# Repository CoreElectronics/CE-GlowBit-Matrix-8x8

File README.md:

# GlowBit™ Matrix 8x8

This is the repo for the Core Electronics [GlowBit Matrix 8x8](https://core-electronics.com.au/catalog/product/view/sku/ce08033).

## License
This project is open source - please review the LICENSE.md file for further licensing information.

If you have any technical questions, or concerns about licensing, please contact technical support on the [Core Electronics forums](https://forum.core-electronics.com.au/).

*\"GlowBit\" and the GlowBit logo are trademarks of Core Electronics Pty Ltd.*

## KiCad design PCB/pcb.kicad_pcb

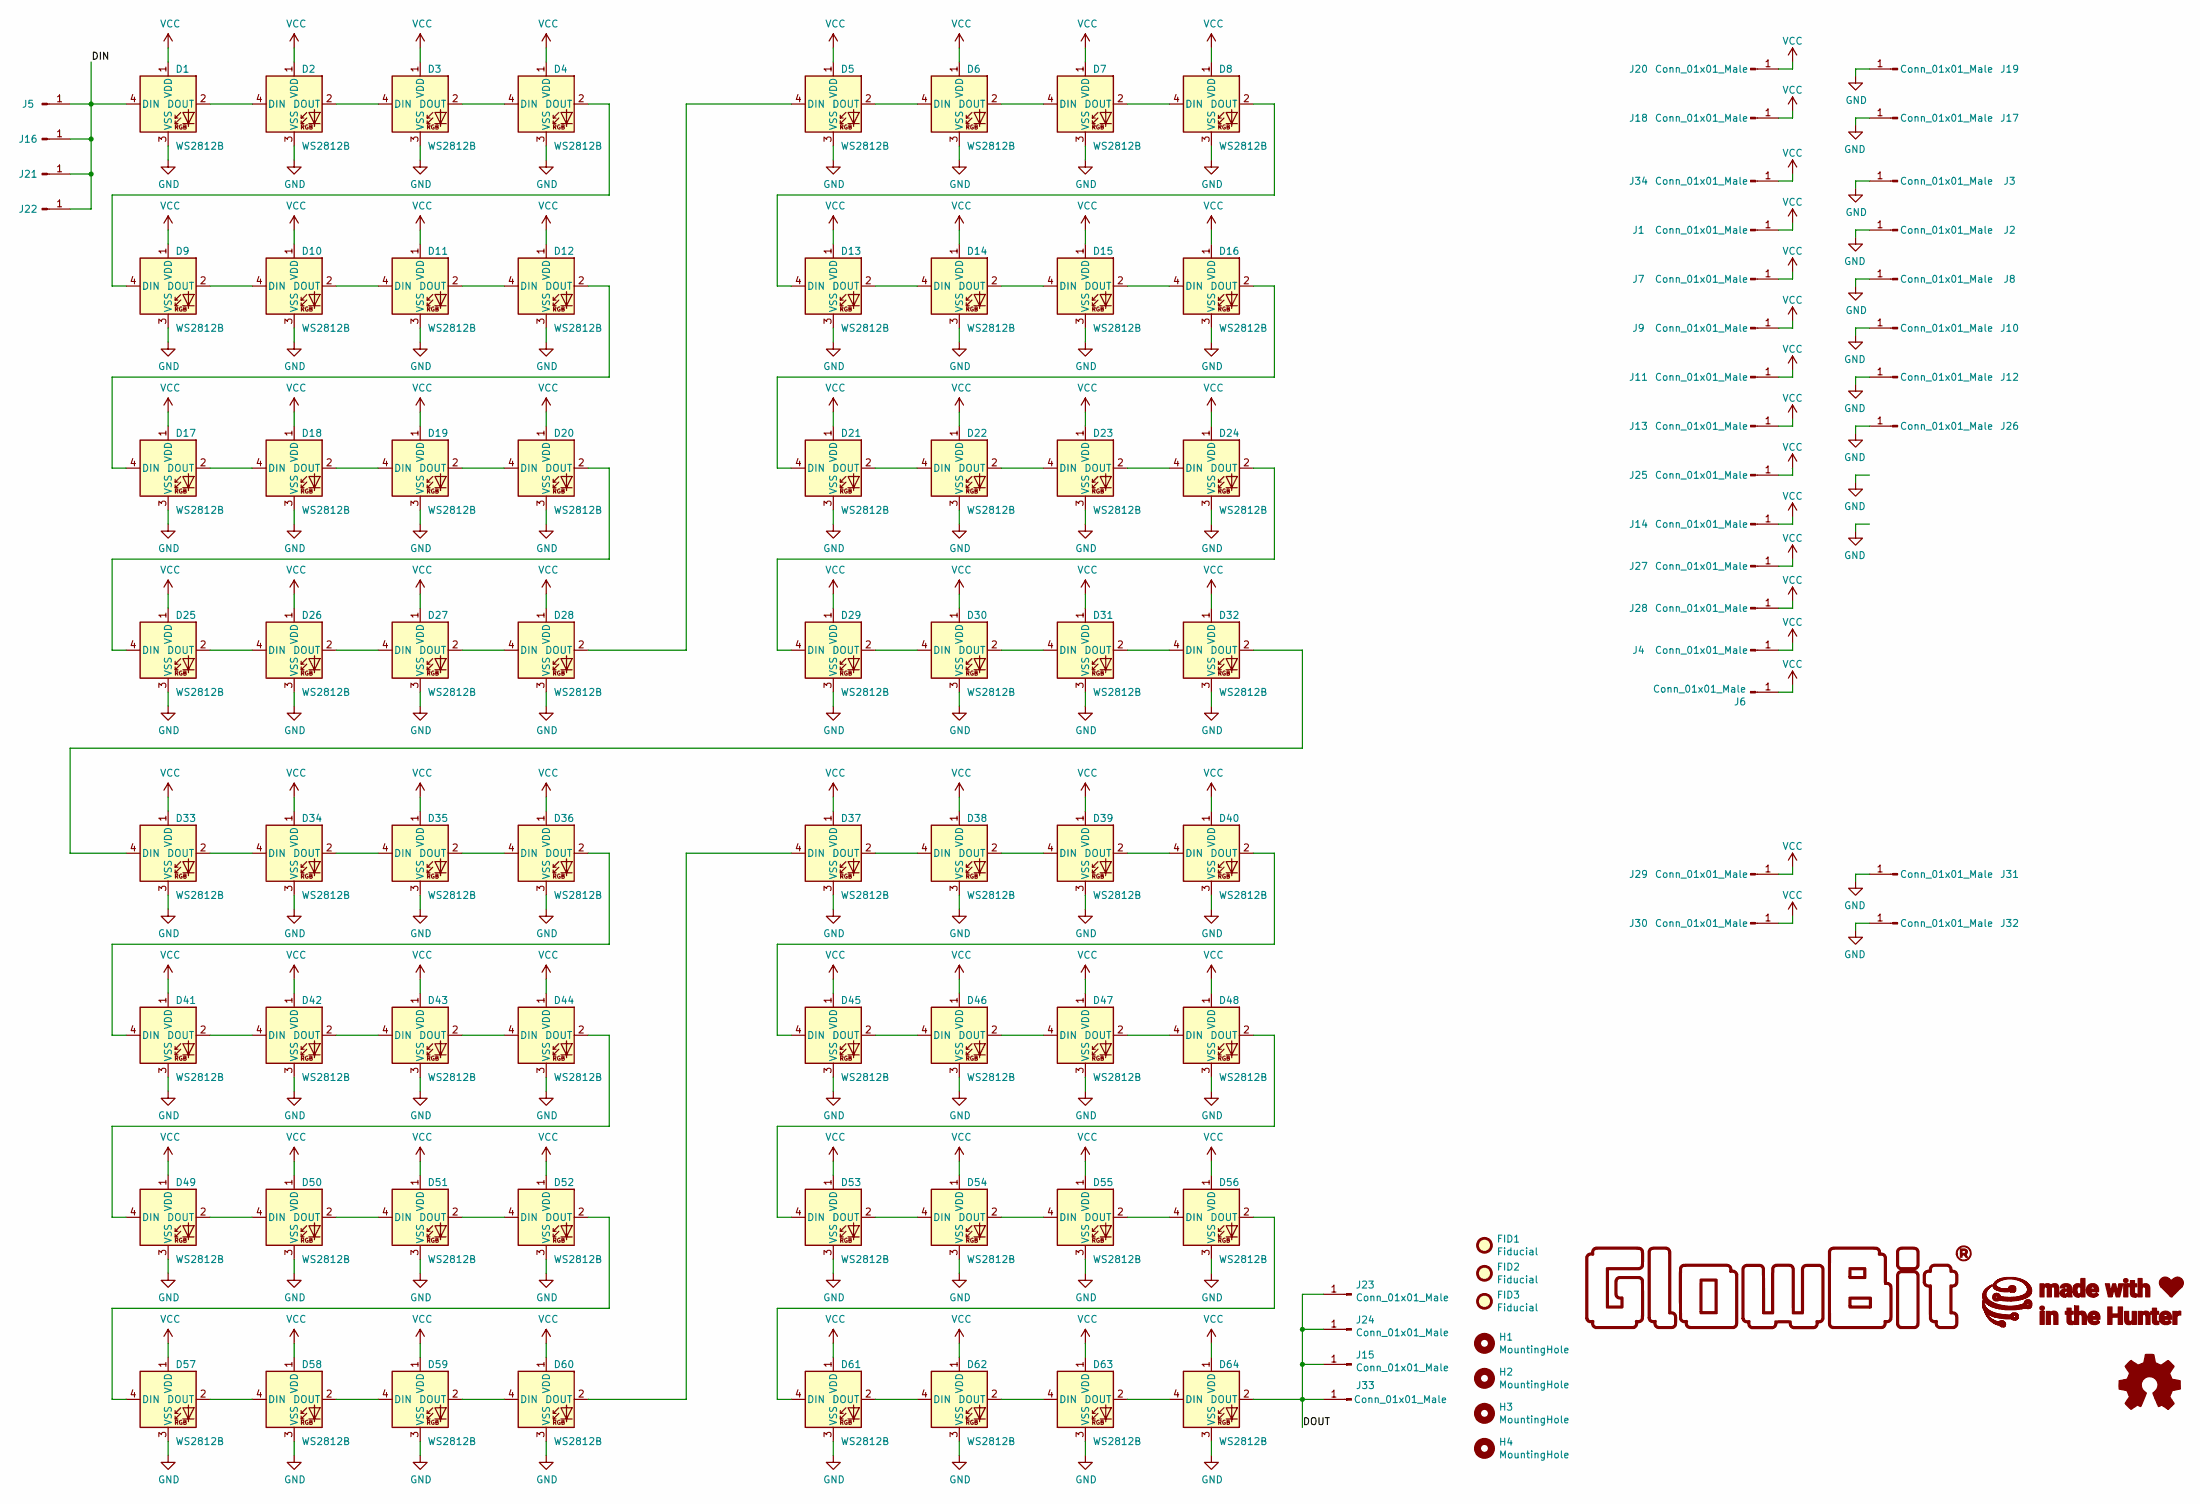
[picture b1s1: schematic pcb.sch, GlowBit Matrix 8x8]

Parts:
D1, D2, D3, D4, D5, D6, D7, D8, D9, D10, D11, D12, D13, D14, D15, D16, D17, D18, D19, D20, D21, D22, D23, D24, D25, D26, D27, D28, D29, D30, D31, D32, D33, D34, D35, D36, D37, D38, D39, D40, D41, D42, D43, D44, D45, D46, D47, D48, D49, D50, D51, D52, D53, D54, D55, D56, D57, D58, D59, D60, D61, D62, D63, D64: WS2812B; LED_GlowBit_WS2812B_NoSilk
FID1, FID2, FID3: Fiducial; Fiducial_1mm_Mask2mm
H1, H2, H3, H4: MountingHole; MountingHole_2.2mm_M2
J1, J6: Conn_01x01_Male; THT-GlowBit-Matrix-Pad-Vcc
J2, J3, J5, J33: Conn_01x01_Male; THT-GlowBit-Matrix-Pad
J4, J7, J9, J11, J13, J14, J18, J20, J25, J27, J28, J34: Conn_01x01_Male; GlowBit-SMD-Pad-Vcc
J8, J10, J12, J15, J16, J17, J19, J21, J22, J23, J24, J26: Conn_01x01_Male; GlowBit-SMD-Pad
J29, J30, J31, J32: Conn_01x01_Male; PowerPad

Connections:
/DIN: D1.4 (DIN), J5.1, J16.1, J21.1, J22.1
/DOUT: D64.2 (DOUT), J15.1, J23.1, J24.1, J33.1
GND: D1.3 (VSS), D2.3 (VSS), D3.3 (VSS), D4.3 (VSS), D5.3 (VSS), D6.3 (VSS), D7.3 (VSS), D8.3 (VSS), D9.3 (VSS), D10.3 (VSS), D11.3 (VSS), D12.3 (VSS), D13.3 (VSS), D14.3 (VSS), D15.3 (VSS), D16.3 (VSS), D17.3 (VSS), D18.3 (VSS), D19.3 (VSS), D20.3 (VSS), D21.3 (VSS), D22.3 (VSS), D23.3 (VSS), D24.3 (VSS), D25.3 (VSS), D26.3 (VSS), D27.3 (VSS), D28.3 (VSS), D29.3 (VSS), D30.3 (VSS), D31.3 (VSS), D32.3 (VSS), D33.3 (VSS), D34.3 (VSS), D35.3 (VSS), D36.3 (VSS), D37.3 (VSS), D38.3 (VSS), D39.3 (VSS), D40.3 (VSS), D41.3 (VSS), D42.3 (VSS), D43.3 (VSS), D44.3 (VSS), D45.3 (VSS), D46.3 (VSS), D47.3 (VSS), D48.3 (VSS), D49.3 (VSS), D50.3 (VSS), D51.3 (VSS), D52.3 (VSS), D53.3 (VSS), D54.3 (VSS), D55.3 (VSS), D56.3 (VSS), D57.3 (VSS), D58.3 (VSS), D59.3 (VSS), D60.3 (VSS), D61.3 (VSS), D62.3 (VSS), D63.3 (VSS), D64.3 (VSS), J2.1, J3.1, J8.1, J10.1, J12.1, J17.1, J19.1, J26.1, J31.1, J32.1
unnamed: D1.2 (DOUT), D2.4 (DIN)
unnamed: D2.2 (DOUT), D3.4 (DIN)
unnamed: D3.2 (DOUT), D4.4 (DIN)
unnamed: D4.2 (DOUT), D9.4 (DIN)
unnamed: D5.2 (DOUT), D6.4 (DIN)
unnamed: D6.2 (DOUT), D7.4 (DIN)
unnamed: D7.2 (DOUT), D8.4 (DIN)
unnamed: D10.2 (DOUT), D11.4 (DIN)
unnamed: D9.2 (DOUT), D10.4 (DIN)
unnamed: D11.2 (DOUT), D12.4 (DIN)
unnamed: D12.2 (DOUT), D17.4 (DIN)
unnamed: D13.2 (DOUT), D14.4 (DIN)
unnamed: D8.2 (DOUT), D13.4 (DIN)
unnamed: D14.2 (DOUT), D15.4 (DIN)
unnamed: D15.2 (DOUT), D16.4 (DIN)
unnamed: D16.2 (DOUT), D21.4 (DIN)
unnamed: D17.2 (DOUT), D18.4 (DIN)
unnamed: D18.2 (DOUT), D19.4 (DIN)
unnamed: D19.2 (DOUT), D20.4 (DIN)
unnamed: D20.2 (DOUT), D25.4 (DIN)
unnamed: D21.2 (DOUT), D22.4 (DIN)
unnamed: D22.2 (DOUT), D23.4 (DIN)
unnamed: D23.2 (DOUT), D24.4 (DIN)
unnamed: D24.2 (DOUT), D29.4 (DIN)
unnamed: D25.2 (DOUT), D26.4 (DIN)
unnamed: D26.2 (DOUT), D27.4 (DIN)
unnamed: D27.2 (DOUT), D28.4 (DIN)
unnamed: D5.4 (DIN), D28.2 (DOUT)
unnamed: D29.2 (DOUT), D30.4 (DIN)
unnamed: D30.2 (DOUT), D31.4 (DIN)
unnamed: D31.2 (DOUT), D32.4 (DIN)
unnamed: D32.2 (DOUT), D33.4 (DIN)
unnamed: D33.2 (DOUT), D34.4 (DIN)
unnamed: D34.2 (DOUT), D35.4 (DIN)
unnamed: D35.2 (DOUT), D36.4 (DIN)
unnamed: D36.2 (DOUT), D41.4 (DIN)
unnamed: D37.2 (DOUT), D38.4 (DIN)
unnamed: D37.4 (DIN), D60.2 (DOUT)
unnamed: D38.2 (DOUT), D39.4 (DIN)
unnamed: D39.2 (DOUT), D40.4 (DIN)
unnamed: D40.2 (DOUT), D45.4 (DIN)
unnamed: D41.2 (DOUT), D42.4 (DIN)
unnamed: D42.2 (DOUT), D43.4 (DIN)
unnamed: D43.2 (DOUT), D44.4 (DIN)
unnamed: D44.2 (DOUT), D49.4 (DIN)
unnamed: D45.2 (DOUT), D46.4 (DIN)
unnamed: D46.2 (DOUT), D47.4 (DIN)
unnamed: D47.2 (DOUT), D48.4 (DIN)
unnamed: D48.2 (DOUT), D53.4 (DIN)
unnamed: D49.2 (DOUT), D50.4 (DIN)
unnamed: D50.2 (DOUT), D51.4 (DIN)
unnamed: D51.2 (DOUT), D52.4 (DIN)
unnamed: D52.2 (DOUT), D57.4 (DIN)
unnamed: D53.2 (DOUT), D54.4 (DIN)
unnamed: D54.2 (DOUT), D55.4 (DIN)
unnamed: D55.2 (DOUT), D56.4 (DIN)
unnamed: D56.2 (DOUT), D61.4 (DIN)
unnamed: D57.2 (DOUT), D58.4 (DIN)
unnamed: D58.2 (DOUT), D59.4 (DIN)
unnamed: D59.2 (DOUT), D60.4 (DIN)
unnamed: D61.2 (DOUT), D62.4 (DIN)
unnamed: D62.2 (DOUT), D63.4 (DIN)
unnamed: D63.2 (DOUT), D64.4 (DIN)
VCC: D1.1 (VDD), D2.1 (VDD), D3.1 (VDD), D4.1 (VDD), D5.1 (VDD), D6.1 (VDD), D7.1 (VDD), D8.1 (VDD), D9.1 (VDD), D10.1 (VDD), D11.1 (VDD), D12.1 (VDD), D13.1 (VDD), D14.1 (VDD), D15.1 (VDD), D16.1 (VDD), D17.1 (VDD), D18.1 (VDD), D19.1 (VDD), D20.1 (VDD), D21.1 (VDD), D22.1 (VDD), D23.1 (VDD), D24.1 (VDD), D25.1 (VDD), D26.1 (VDD), D27.1 (VDD), D28.1 (VDD), D29.1 (VDD), D30.1 (VDD), D31.1 (VDD), D32.1 (VDD), D33.1 (VDD), D34.1 (VDD), D35.1 (VDD), D36.1 (VDD), D37.1 (VDD), D38.1 (VDD), D39.1 (VDD), D40.1 (VDD), D41.1 (VDD), D42.1 (VDD), D43.1 (VDD), D44.1 (VDD), D45.1 (VDD), D46.1 (VDD), D47.1 (VDD), D48.1 (VDD), D49.1 (VDD), D50.1 (VDD), D51.1 (VDD), D52.1 (VDD), D53.1 (VDD), D54.1 (VDD), D55.1 (VDD), D56.1 (VDD), D57.1 (VDD), D58.1 (VDD), D59.1 (VDD), D60.1 (VDD), D61.1 (VDD), D62.1 (VDD), D63.1 (VDD), D64.1 (VDD), J1.1, J4.1, J6.1, J7.1, J9.1, J11.1, J13.1, J14.1, J18.1, J20.1, J25.1, J27.1, J28.1, J29.1, J30.1, J34.1

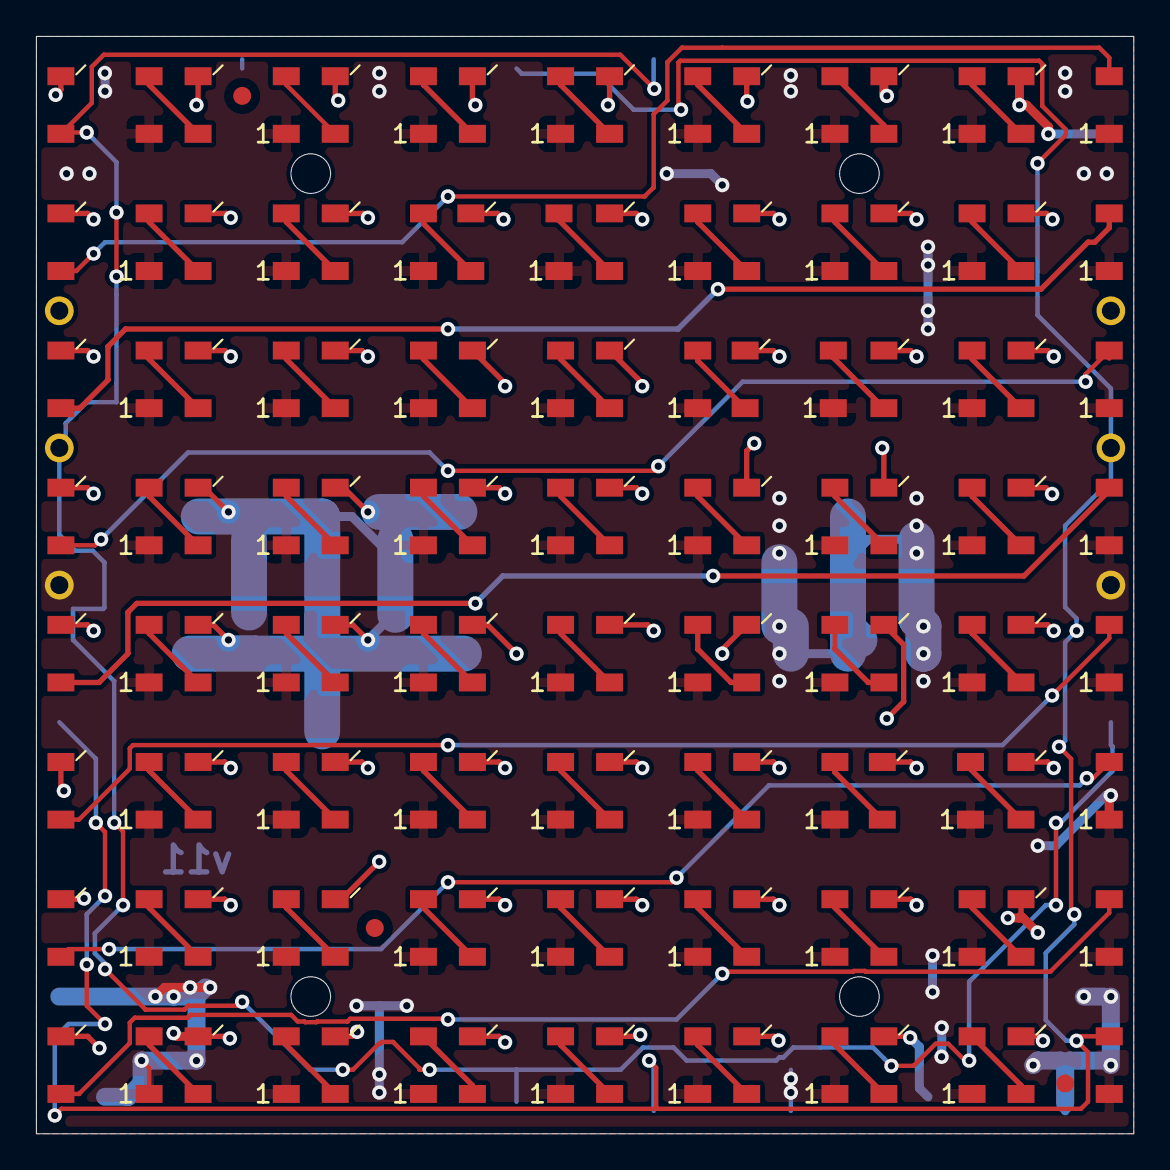
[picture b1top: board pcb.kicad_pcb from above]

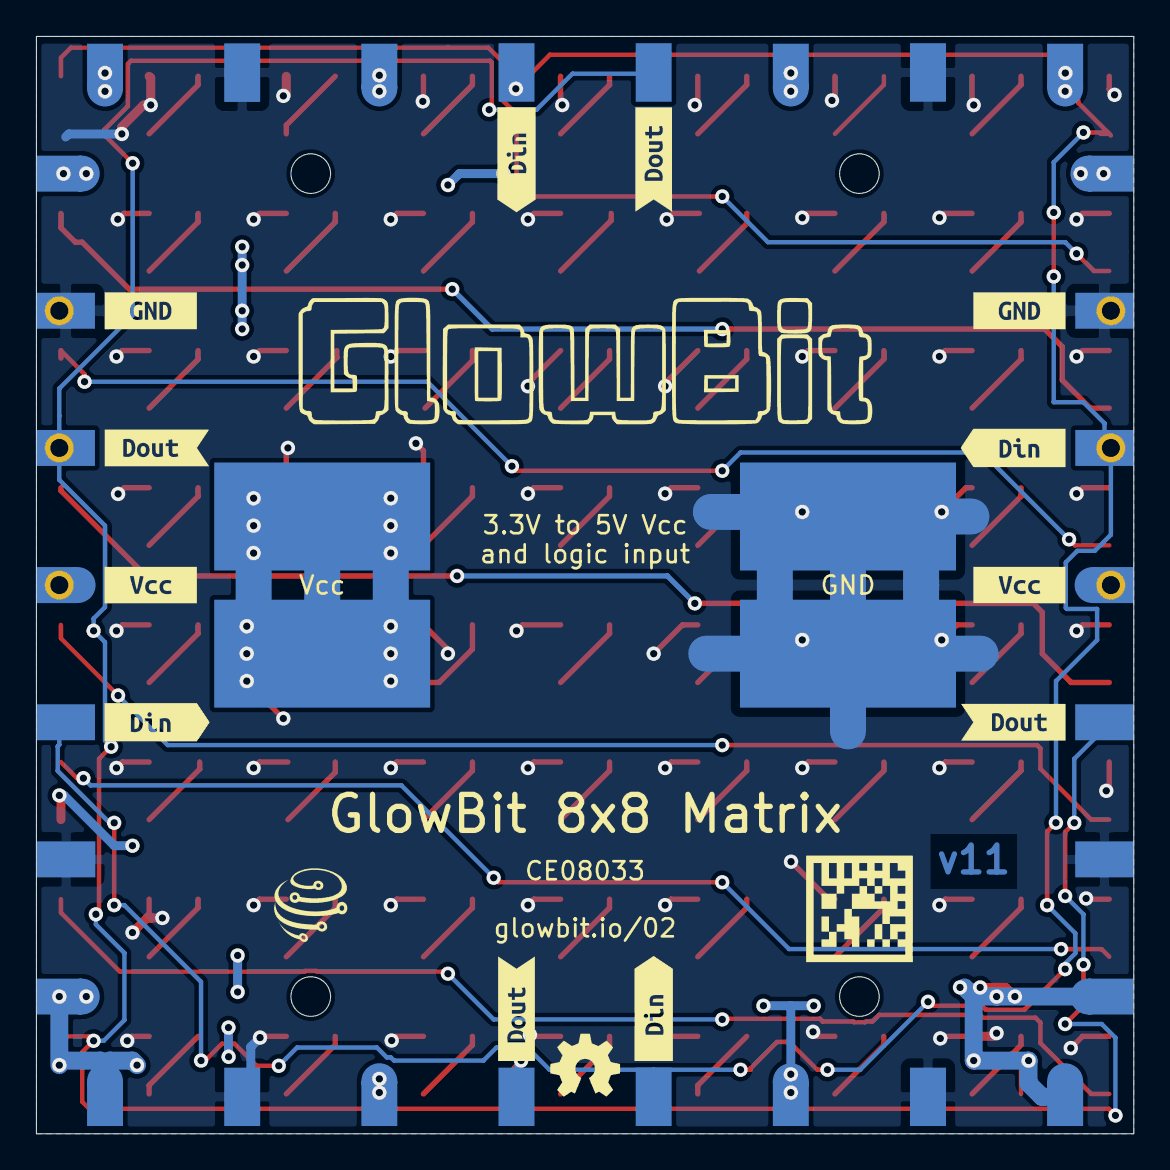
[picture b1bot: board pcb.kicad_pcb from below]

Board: 2 copper layers, 61.0 x 61.0 mm, 119 parts (18 on the bottom side), 67 nets.

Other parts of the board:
G1: LOGO; Glowbit-31.9x7.0mm
G2: LOGO: OSHW; oshw_3.9x3.5mm
kibuzzard-6119FB4C, kibuzzard-6119FB4C#2: G5; label
kibuzzard-6119FB06, kibuzzard-6119FB06#2: G6; label
kibuzzard-6119FB8F: G8; label
kibuzzard-6119FB8F#2: G13; label
kibuzzard-6119FBA7: G3; label
kibuzzard-6119FBA7#2: G10; label
kibuzzard-61259FA5, kibuzzard-61259FA5#2, kibuzzard-61259FD0, kibuzzard-61259FD0#2: G***; label

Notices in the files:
PCB/pcb.kicad_pcb:
License: CCASAv4.0 https://creativecommons.org/licenses/by-sa/4.0
